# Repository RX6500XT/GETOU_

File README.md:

# GETOU_
Its a portable macropad but the power is on a separate PCB

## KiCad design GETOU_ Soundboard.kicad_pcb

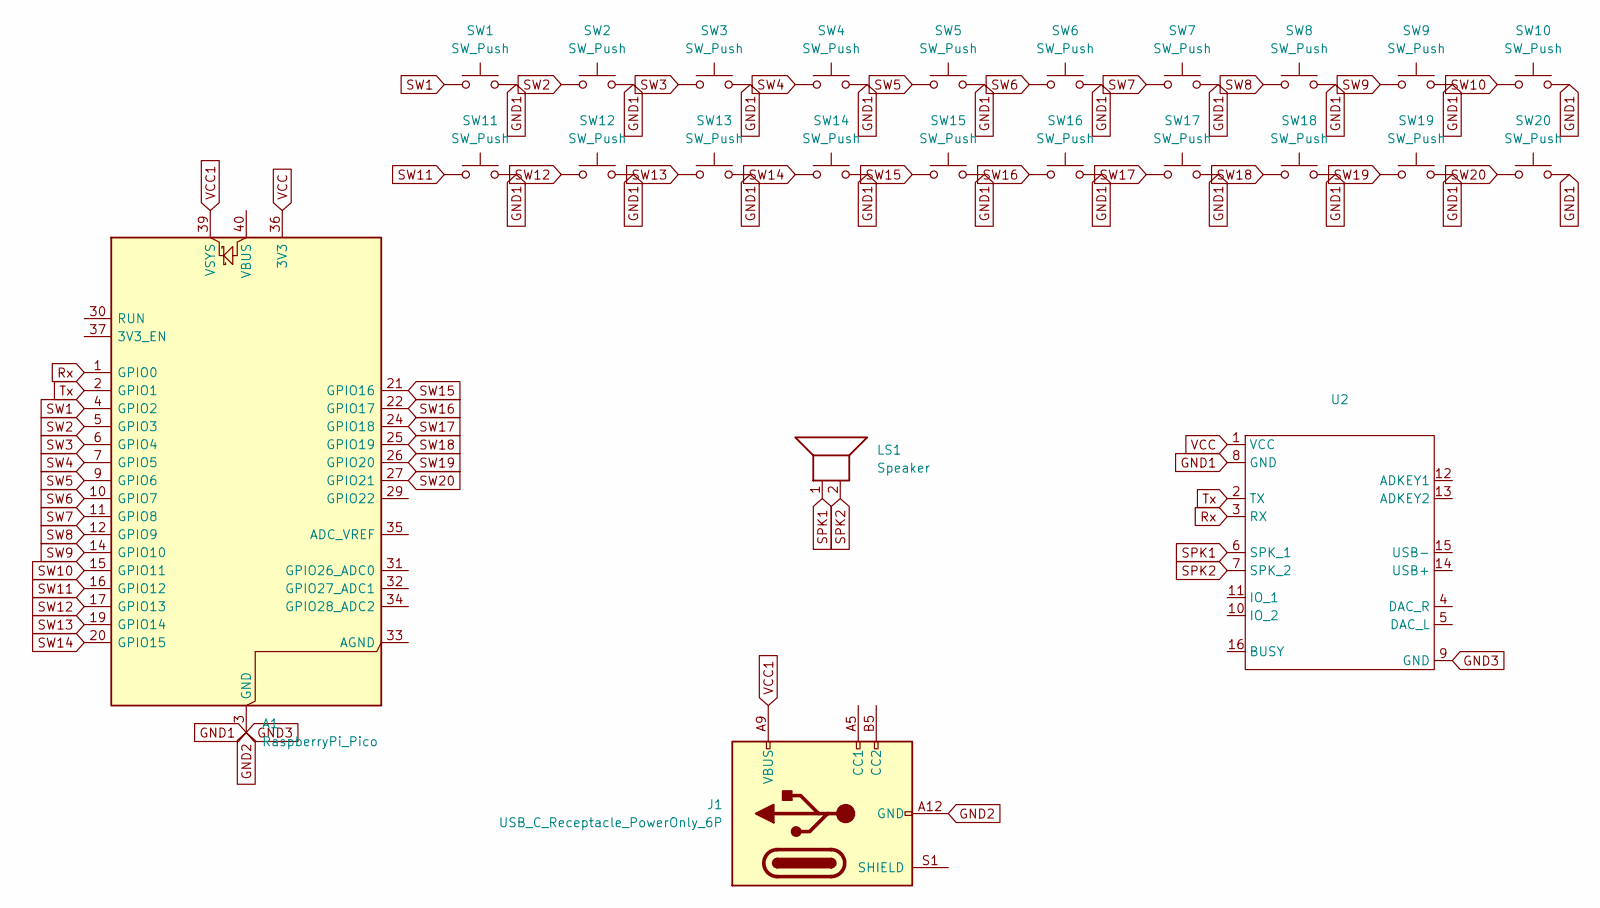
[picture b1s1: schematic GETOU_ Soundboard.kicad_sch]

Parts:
A1: RaspberryPi_Pico; RaspberryPi_Pico_Common_Unspecified
J1: USB_C_Receptacle_PowerOnly_6P; USB_C_Receptacle_GCT_USB4085
LS1: Speaker; SP500208‑3
SW1, SW2, SW3, SW4, SW5, SW6, SW7, SW8, SW9, SW10, SW11, SW12, SW13, SW14, SW15, SW16, SW17, SW18, SW19, SW20: SW_Push; SW_PUSH_6mm_H4.3mm
U2: DFPlayer Mini

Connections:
GND1: A1.3 (GND), A1.8 (GND), A1.13 (GND), A1.18 (GND), A1.23 (GND), A1.28 (GND), A1.38 (GND), J1.A12 (GND), J1.B12 (GND), SW1.2, SW2.2, SW3.2, SW4.2, SW5.2, SW6.2, SW7.2, SW8.2, SW9.2, SW10.2, SW11.2, SW12.2, SW13.2, SW14.2, SW15.2, SW16.2, SW17.2, SW18.2, SW19.2, SW20.2, U2.8 (GND), U2.9 (GND)
Rx: A1.1 (GPIO0), U2.3 (RX)
SPK1: LS1.1, U2.6 (SPK_1)
SPK2: LS1.2, U2.7 (SPK_2)
SW1: A1.4 (GPIO2), SW1.1
SW2: A1.5 (GPIO3), SW2.1
SW3: A1.6 (GPIO4), SW3.1
SW4: A1.7 (GPIO5), SW4.1
SW5: A1.9 (GPIO6), SW5.1
SW6: A1.10 (GPIO7), SW6.1
SW7: A1.11 (GPIO8), SW7.1
SW8: A1.12 (GPIO9), SW8.1
SW9: A1.14 (GPIO10), SW9.1
SW10: A1.15 (GPIO11), SW10.1
SW11: A1.16 (GPIO12), SW11.1
SW12: A1.17 (GPIO13), SW12.1
SW13: A1.19 (GPIO14), SW13.1
SW14: A1.20 (GPIO15), SW14.1
SW15: A1.21 (GPIO16), SW15.1
SW16: A1.22 (GPIO17), SW16.1
SW17: A1.24 (GPIO18), SW17.1
SW18: A1.25 (GPIO19), SW18.1
SW19: A1.26 (GPIO20), SW19.1
SW20: A1.27 (GPIO21), SW20.1
Tx: A1.2 (GPIO1), U2.2 (TX)
VCC: A1.36 (3V3), U2.1 (VCC)
VCC1: A1.39 (VSYS), J1.A9 (VBUS), J1.B9 (VBUS)

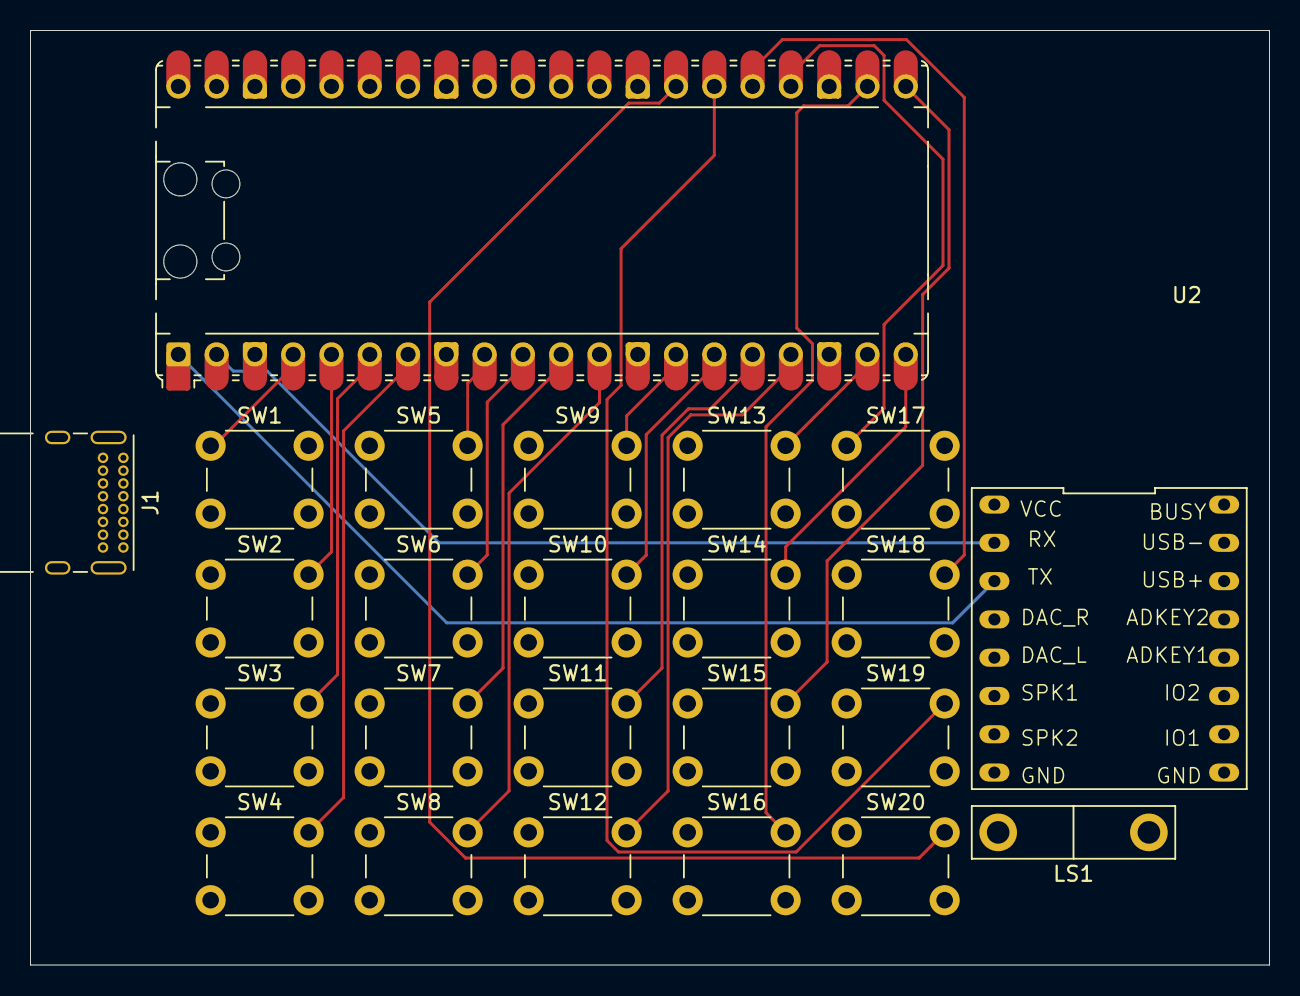
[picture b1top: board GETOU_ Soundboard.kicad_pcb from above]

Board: 4 copper layers, 82.2 x 62.0 mm, 24 parts (0 on the bottom side), 27 nets.
